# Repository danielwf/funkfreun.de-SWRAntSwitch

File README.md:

# funkfreun.de-SWRAntSwitch

Moved to easyEDA -> https://u.easyeda.com/join?type=project&key=534c346b386687a74989fcf1c03e5253&inviter=55e5144d4fb84874899f82d5ca26546c

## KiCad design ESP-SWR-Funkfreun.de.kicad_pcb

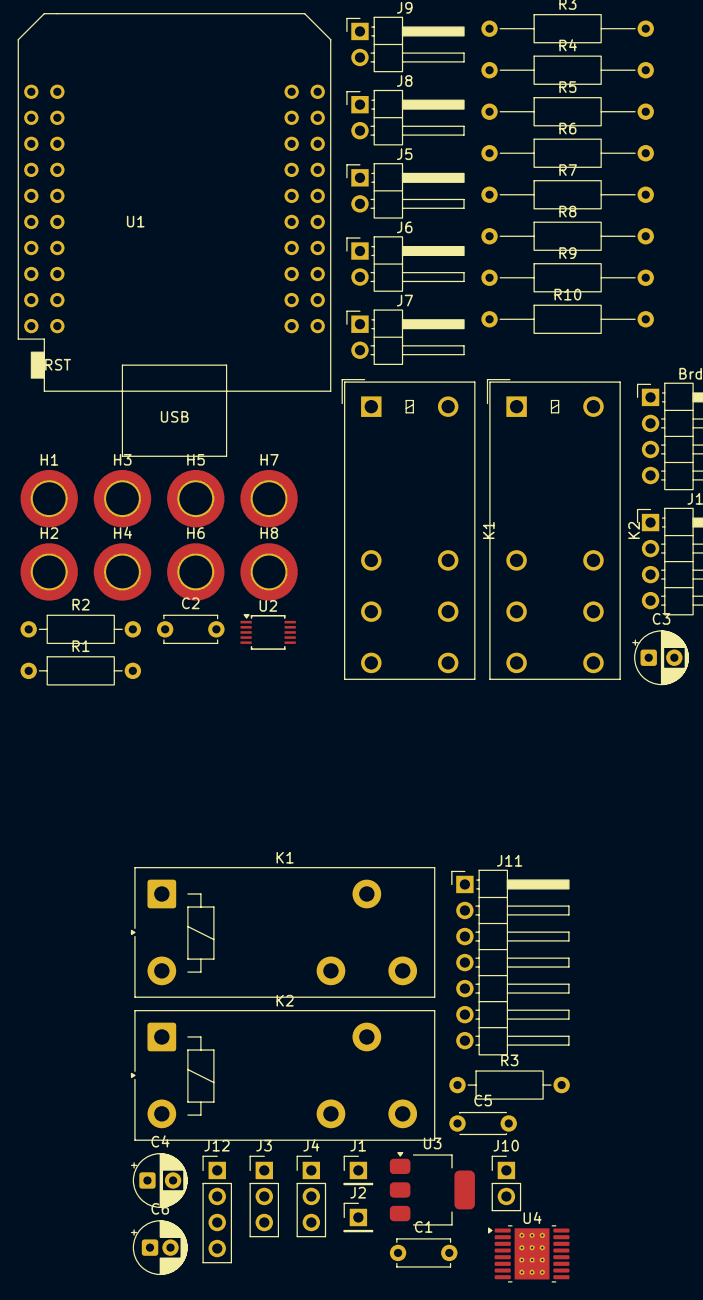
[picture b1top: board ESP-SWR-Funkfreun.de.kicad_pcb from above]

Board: 2 copper layers, 47 parts (0 on the bottom side), 35 nets, no tracks yet.

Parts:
Brd1: SSD1306; PinHeader_1x04_P2.54mm_Horizontal
C1, C2: 100n; C_Disc_D5.0mm_W2.5mm_P5.00mm
C3, C4: 4.7u; CP_Radial_D5.0mm_P2.50mm
C5: 100nF; C_Disc_D4.3mm_W1.9mm_P5.00mm
C6: 2.2uF; CP_Radial_D5.0mm_P2.00mm
H1, H2, H3, H4, H5, H6, H7, H8: Mnt.Hole; MountingHole_3.2mm_M3_DIN965_Pad_TopBottom
J1: Batt-; PinHeader_1x01_P2.54mm_Vertical
J1#2: Conn_01x04_Pin; PinHeader_1x04_P2.54mm_Horizontal
J2: Batt+; PinHeader_1x01_P2.54mm_Vertical
J3: SWR1; PinHeader_1x03_P2.54mm_Vertical
J4: SWR2; PinHeader_1x03_P2.54mm_Vertical
J5: SWR-OUT; PinHeader_1x02_P2.54mm_Horizontal
J6: SWR-IN; PinHeader_1x02_P2.54mm_Horizontal
J7: TRX; PinHeader_1x02_P2.54mm_Horizontal
J8: ANT2; PinHeader_1x02_P2.54mm_Horizontal
J9: ANT1; PinHeader_1x02_P2.54mm_Horizontal
J10: Button; PinHeader_1x02_P2.54mm_Vertical
J11: GC9A01; PinHeader_1x07_P2.54mm_Horizontal
J12: Conn_01x04; PinHeader_1x04_P2.54mm_Vertical
K1, K2#2: Finder 40.31.6.006.0000; Relay_SPDT_Finder_40.31
K1#2, K2: Omron G5RL; Relay_DPDT_Omron_G2RL-2
R1, R2, R3: 10k; R_Axial_DIN0207_L6.3mm_D2.5mm_P10.16mm_Horizontal
R3#2, R4, R5, R6, R7, R8, R9, R10: 50R; R_Axial_DIN0207_L6.3mm_D2.5mm_P15.24mm_Horizontal
U1: mini_esp32; ESP32_mini
U2: ADS1115IDGS; TSSOP-10_3x3mm_P0.5mm
U3: AMS1117-5.0; SOT-223-3_TabPin2
U4: DRV8833PWP; HTSSOP-16-1EP_4.4x5mm_P0.65mm_EP3.4x5mm_Mask2.46x2.31mm_The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

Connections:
5V: C4.2, U1.35 (VCC_(USB)), U3.2 (VO), U4.12 (VM)
+3.3V: Brd1.2 (VCC), C2.1, C3.1, J11.1, J12.3, R1.1, R2.1, R3.1, U1.16 (3V3), U2.8 (VDD)
-BATT: Brd1.1 (GND), R7.1, R8.1, R9.1, R10.1
GND: C1.2, C2.2, C3.2, C4.1, C5.1, C6.2, H1.1, H2.1, H3.1, H4.1, H5.1, H6.1, H7.1, H8.1, J1.1, J3.2, J4.2, J5.1, J6.1, J7.1, J8.1, J9.1, J10.1, J11.2, J12.4, K1.14, K2#2.12, U1.1 (GND), U1.22 (GND), U1.33 (GND), U2.3 (GND), U3.1 (GND), U4.3 (AISEN), U4.6 (BISEN), U4.13 (GND), U4.17 (GND)
unnamed: C1.1, J2.1, U3.3 (VI)
unnamed: K1#2.11, K1#2.21
unnamed: J3.1, U2.4 (AIN0)
unnamed: K2.11, K2.21
unnamed: J3.3, U2.5 (AIN1)
unnamed: J4.1, U2.6 (AIN2)
unnamed: K1#2.12, K1#2.22, K2.14, K2.24
unnamed: J4.3, U2.7 (AIN3)
unnamed: J5.2, K1.12, K2#2.14
unnamed: J6.2, J7.2
unnamed: J8.2, K2#2.11
unnamed: J9.2, K1.11
unnamed: J10.2, R3.2, U1.11 (IO_34)
unnamed: J12.1, R2.2, U1.27 (IO_21/D2/SDA), U2.9 (SDA)
unnamed: J12.2, R1.2, U1.25 (IO_22/D1/SCL), U2.10 (SCL)
unnamed: K1#2.14, K1#2.24, R3#2.2, R4.2
unnamed: K2.12, K2.22, R5.2, R6.2
unnamed: R5.1, R6.1, R7.2, R8.2
unnamed: R3#2.1, R4.1, R9.2, R10.2
unnamed: U1.26 (IO_25), U4.15 (AIN2)
unnamed: U1.24 (IO_27), U4.16 (AIN1)
unnamed: C5.2, U4.11 (VCP)
unnamed: C6.1, U4.14 (VINT)
Relais_A1: K1.A1, K2#2.A1, U4.2 (AOUT1)
Relais_A2: K1.A2, K2#2.A2, U4.4 (AOUT2)
SPI_CLK: J11.3, U1.8 (IO_18/D5)
SPI_CS: J11.6, U1.29 (IO_17/D3)
SPI_DATA/MOSI: J11.4, U1.12 (IO_23/D7)
SPI_DC: J11.5, U1.31 (IO_16/D4)
SPI_RST: J11.7, U1.32 (IO_04)
nSleep: U1.6 (IO_26/D0), U4.1 (~SLEEP)
